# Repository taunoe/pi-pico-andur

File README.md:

# Pi Pico Andur

## Proto 0

- https://www.instagram.com/reel/DPMSu_giLpH/?utm_source=ig_web_copy_link&igsh=MzRlODBiNWFlZA==
- https://www.instagram.com/reel/DPefCeejA3R/?utm_source=ig_web_copy_link&igsh=MzRlODBiNWFlZA==

## Proto 1 Jupid

Pilt|Nimi    | m    | m   |Kood
----|--------|------|-----|----
|RASPBERRY PI PICO 2| Cortex-M33| |SC1631
|ToF / Laser moodul| VL53L0X 3-5VDC| I2C, 0.05÷1.2m | OKYN220420-17
|OLED display| 0.96''| Sinine ja valge| OKY4020
|Toitemoodul DC/DC| step-down |4.75..23V/1..17 3A|OKY3504-1
|Rotary Encoder|-|-| OKY3431
|Makettplaat| 40*60mm |-|OKY0001-1-4X6CM
|Makettplaat| 20*80mm| kahepoolne| OKN426-8
|LED punane matt| 2*5mm| 5mcd| OLC2X5M0005
|LED roheline matt| 2*5mm| 10mcd| LZ2X5M0010
|Takisti | 470R | 1/4W| -
|Optron|EL817C |-| PC817
|Toitepesa paneelile| 2.1/5.5mm| | PC-010
|Pistik| 2.1/5.5mm| 14mm, plast| LUM-XNESJ210
|Signalisatsioonikaabel|8x0.22mm2 |tinatatud Valge|S8X022W
|Lintkaabel| 5*0.3mm2|-| LP05-RGBW
|Piikriba |1*40pin| 2.54mm|CC078
|Piikriba pesa plaadile| 1*20pin |2.54mm |L20420GS
|Kruviklemmliist| 12*2.5mm2| STCM-8471| EL-CONN040B
|2-ne klemmliist pcb| 5.0mm| h=10mm 1.5mm2| TB-001LC
|3-ne klemmiist. pcb| 5.0mm| h=12mm| TB-002
|Ühendusklemm 3-ne| kangiga avatav ja suletav|-| DGBSC-SG01/4-03P
|Ühendusklemm 2-ne| kangiga| läbiv|DGBSC-SG02/4-01P
|Kaablisideme komplekt| 160mm| Värvilised| ECTC160

Tauno Erik 2025

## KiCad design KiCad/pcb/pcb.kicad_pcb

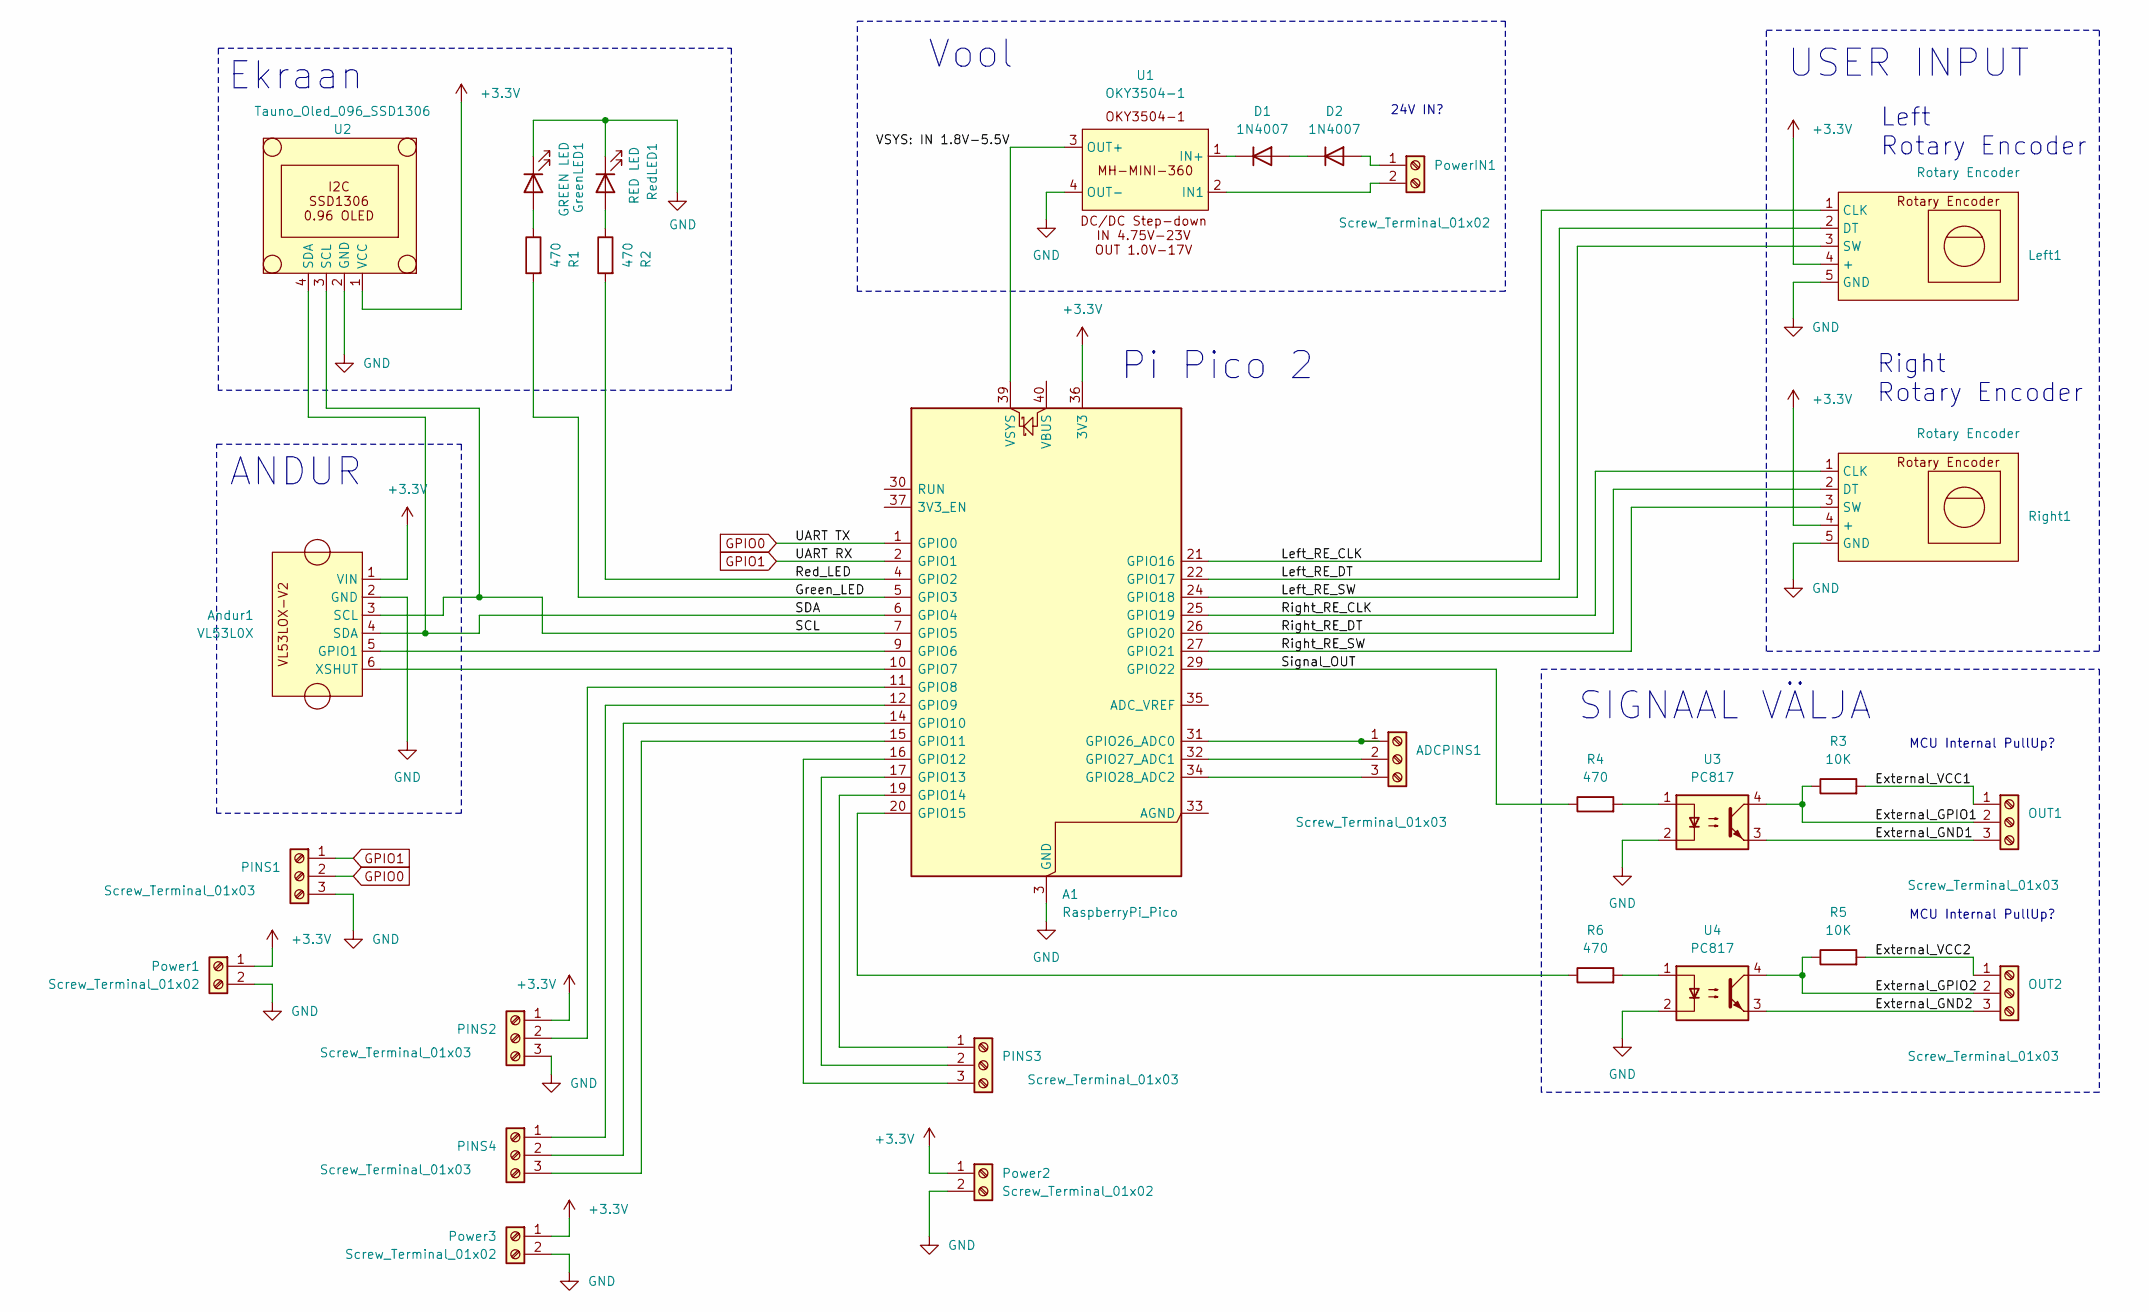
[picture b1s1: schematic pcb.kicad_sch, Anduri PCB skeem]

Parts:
A1: RaspberryPi_Pico; RaspberryPi_Pico_W_SMD_HandSolder
ADCPINS1: Screw_Terminal_01x03; TerminalBlock_MaiXu_MX126-5.0-03P_1x03_P5.00mm
Andur1: VL53L0X; TerminalBlock_MaiXu_MX126-5.0-06P_1x06_P5.00mm
D1, D2: 1N4007; D_DO-41_SOD81_P10.16mm_Horizontal
GreenLED1: GREEN LED; LED_Rectangular_W5.0mm_H2.0mm
Left1: Rotary Encoder; Tauno_Rotary_Encoder
OUT1, OUT2: Screw_Terminal_01x03; TerminalBlock_MaiXu_MX126-5.0-03P_1x03_P5.00mm
PINS1, PINS2, PINS3, PINS4: Screw_Terminal_01x03; TerminalBlock_MaiXu_MX126-5.0-03P_1x03_P5.00mm
Power1, Power2, Power3: Screw_Terminal_01x02; TerminalBlock_MaiXu_MX126-5.0-02P_1x02_P5.00mm
PowerIN1: Screw_Terminal_01x02; TerminalBlock_MaiXu_MX126-5.0-02P_1x02_P5.00mm
R1, R2, R4, R6: 470; R_Axial_DIN0207_L6.3mm_D2.5mm_P10.16mm_Horizontal
R3, R5: 10K; R_Axial_DIN0207_L6.3mm_D2.5mm_P10.16mm_Horizontal
RedLED1: RED LED; LED_Rectangular_W5.0mm_H2.0mm
Right1: Rotary Encoder; Tauno_Rotary_Encoder
U1: OKY3504-1; Tauno_OKY3504
U2: Tauno_Oled_096_SSD1306; Tauno_OLED_ssd1306
U3, U4: PC817; DIP-4_W7.62mm

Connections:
+3.3V: A1.36 (3V3), Andur1.1 (VIN), Left1.4 (+), PINS2.1, Power1.1, Power2.1, Power3.1, Right1.4 (+), U2.1 (VCC)
/External_GND1: OUT1.3, U3.3
/External_GND2: OUT2.3, U4.3
/External_GPIO1: OUT1.2, R3.1, U3.4
/External_GPIO2: OUT2.2, R5.1, U4.4
/External_VCC1: OUT1.1, R3.2
/External_VCC2: OUT2.1, R5.2
/Green_LED: A1.5 (GPIO3), R1.2
/Left_RE_CLK: A1.21 (GPIO16), Left1.1 (CLK)
/Left_RE_DT: A1.22 (GPIO17), Left1.2 (DT)
/Left_RE_SW: A1.24 (GPIO18), Left1.3 (SW)
/Red_LED: A1.4 (GPIO2), R2.2
/Right_RE_CLK: A1.25 (GPIO19), Right1.1 (CLK)
/Right_RE_DT: A1.26 (GPIO20), Right1.2 (DT)
/Right_RE_SW: A1.27 (GPIO21), Right1.3 (SW)
/SCL: A1.7 (GPIO5), Andur1.3 (SCL), U2.3 (SCL)
/SDA: A1.6 (GPIO4), Andur1.4 (SDA), U2.4 (SDA)
/Signal_OUT: A1.29 (GPIO22), R4.1
/VSYS: IN 1.8V-5.5V: A1.39 (VSYS), U1.3 (OUT+)
GND: A1.3 (GND), A1.8 (GND), A1.13 (GND), A1.18 (GND), A1.23 (GND), A1.28 (GND), A1.38 (GND), Andur1.2 (GND), GreenLED1.1 (K), Left1.5 (GND), PINS1.3, PINS2.3, Power1.2, Power2.2, Power3.2, RedLED1.1 (K), Right1.5 (GND), U1.4 (OUT-), U2.2 (GND), U3.2, U4.2
GPIO0: A1.1 (GPIO0), PINS1.2
GPIO1: A1.2 (GPIO1), PINS1.1
unnamed: A1.9 (GPIO6), Andur1.5 (GPIO1)
unnamed: A1.10 (GPIO7), Andur1.6 (XSHUT)
unnamed: A1.11 (GPIO8), PINS2.2
unnamed: A1.12 (GPIO9), PINS4.1
unnamed: A1.14 (GPIO10), PINS4.2
unnamed: A1.15 (GPIO11), PINS4.3
unnamed: A1.16 (GPIO12), PINS3.3
unnamed: A1.17 (GPIO13), PINS3.2
unnamed: A1.19 (GPIO14), PINS3.1
unnamed: A1.20 (GPIO15), R6.1
unnamed: A1.31 (GPIO26_ADC0), ADCPINS1.1
unnamed: A1.32 (GPIO27_ADC1), ADCPINS1.2
unnamed: A1.34 (GPIO28_ADC2), ADCPINS1.3
unnamed: D1.2 (A), D2.1 (K)
unnamed: D1.1 (K), U1.1 (IN+)
unnamed: D2.2 (A), PowerIN1.1
unnamed: GreenLED1.2 (A), R1.1
unnamed: PowerIN1.2, U1.2 (IN1)
unnamed: R4.2, U3.1
unnamed: R6.2, U4.1
unnamed: R2.1, RedLED1.2 (A)

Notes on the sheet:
Right Rotary Encoder
Ekraan
Vool
ANDUR
MCU Internal PullUp?
Pi Pico 2
SIGNAAL VÄLJA
USER INPUT
24V IN?
Left Rotary Encoder

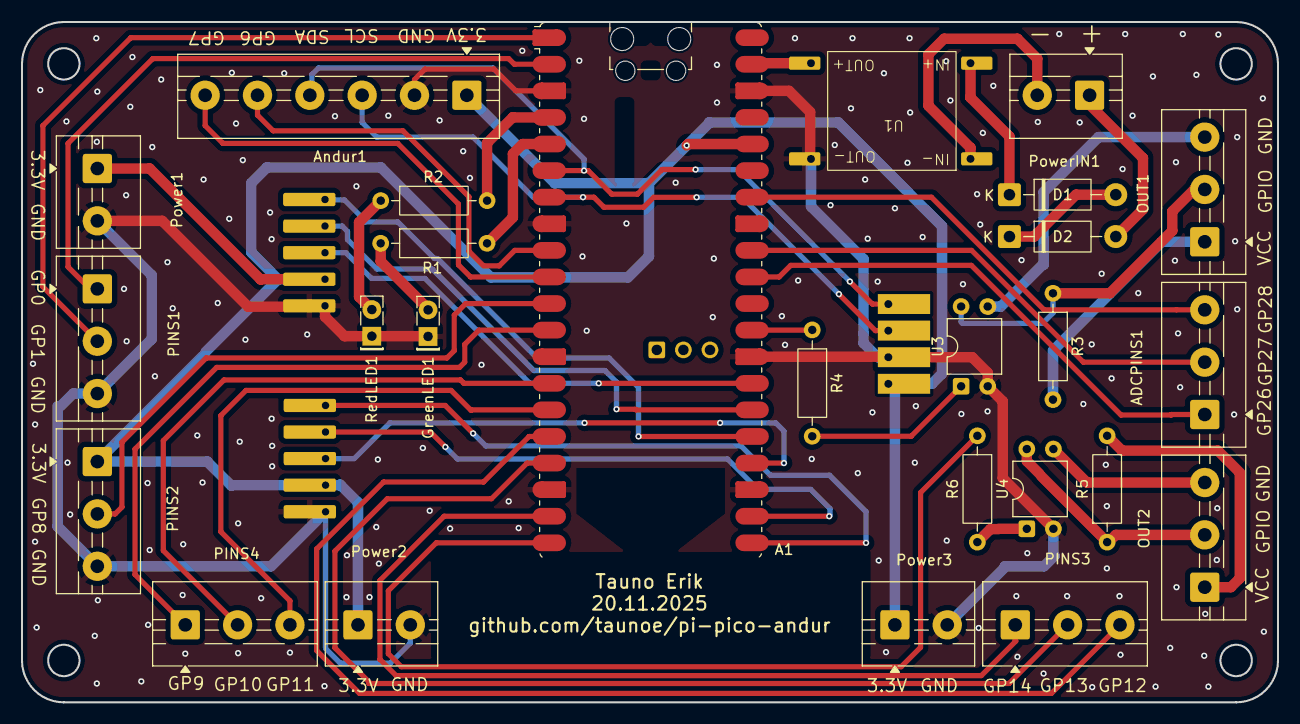
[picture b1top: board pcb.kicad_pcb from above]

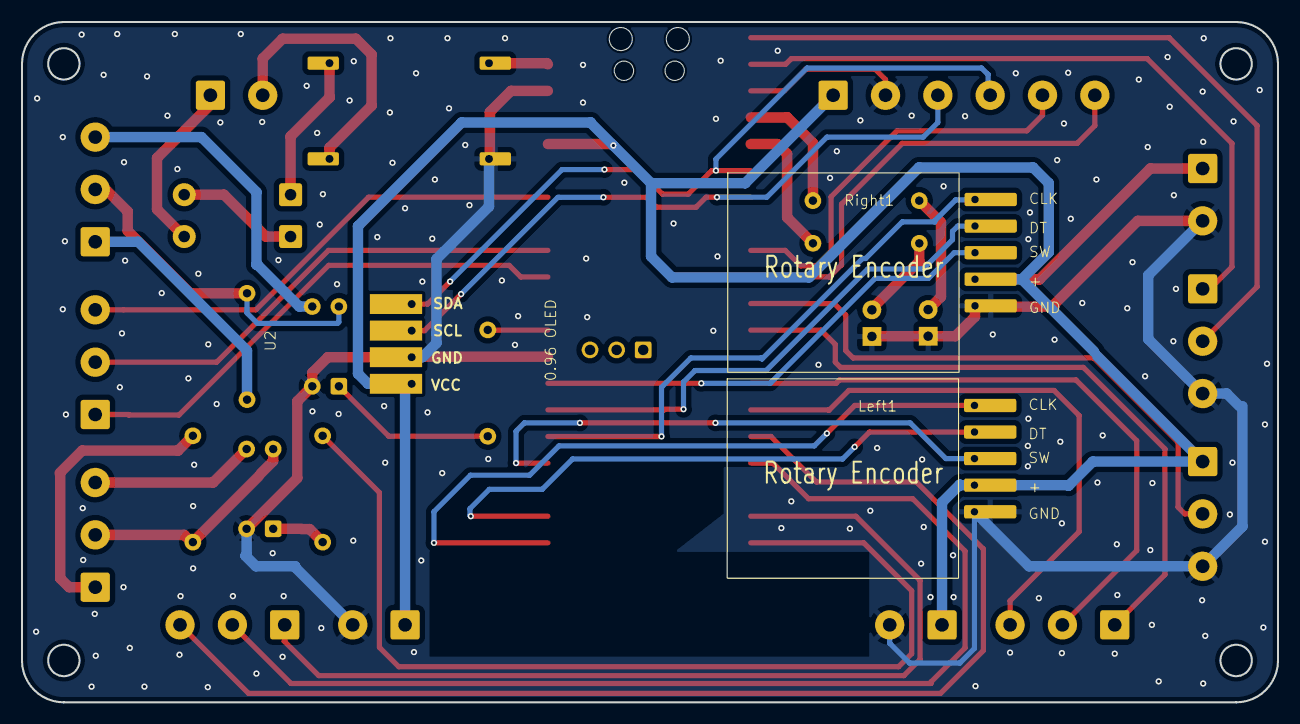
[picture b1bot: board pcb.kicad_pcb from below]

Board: 2 copper layers, 120.0 x 65.0 mm, 29 parts (3 on the bottom side), 43 nets.

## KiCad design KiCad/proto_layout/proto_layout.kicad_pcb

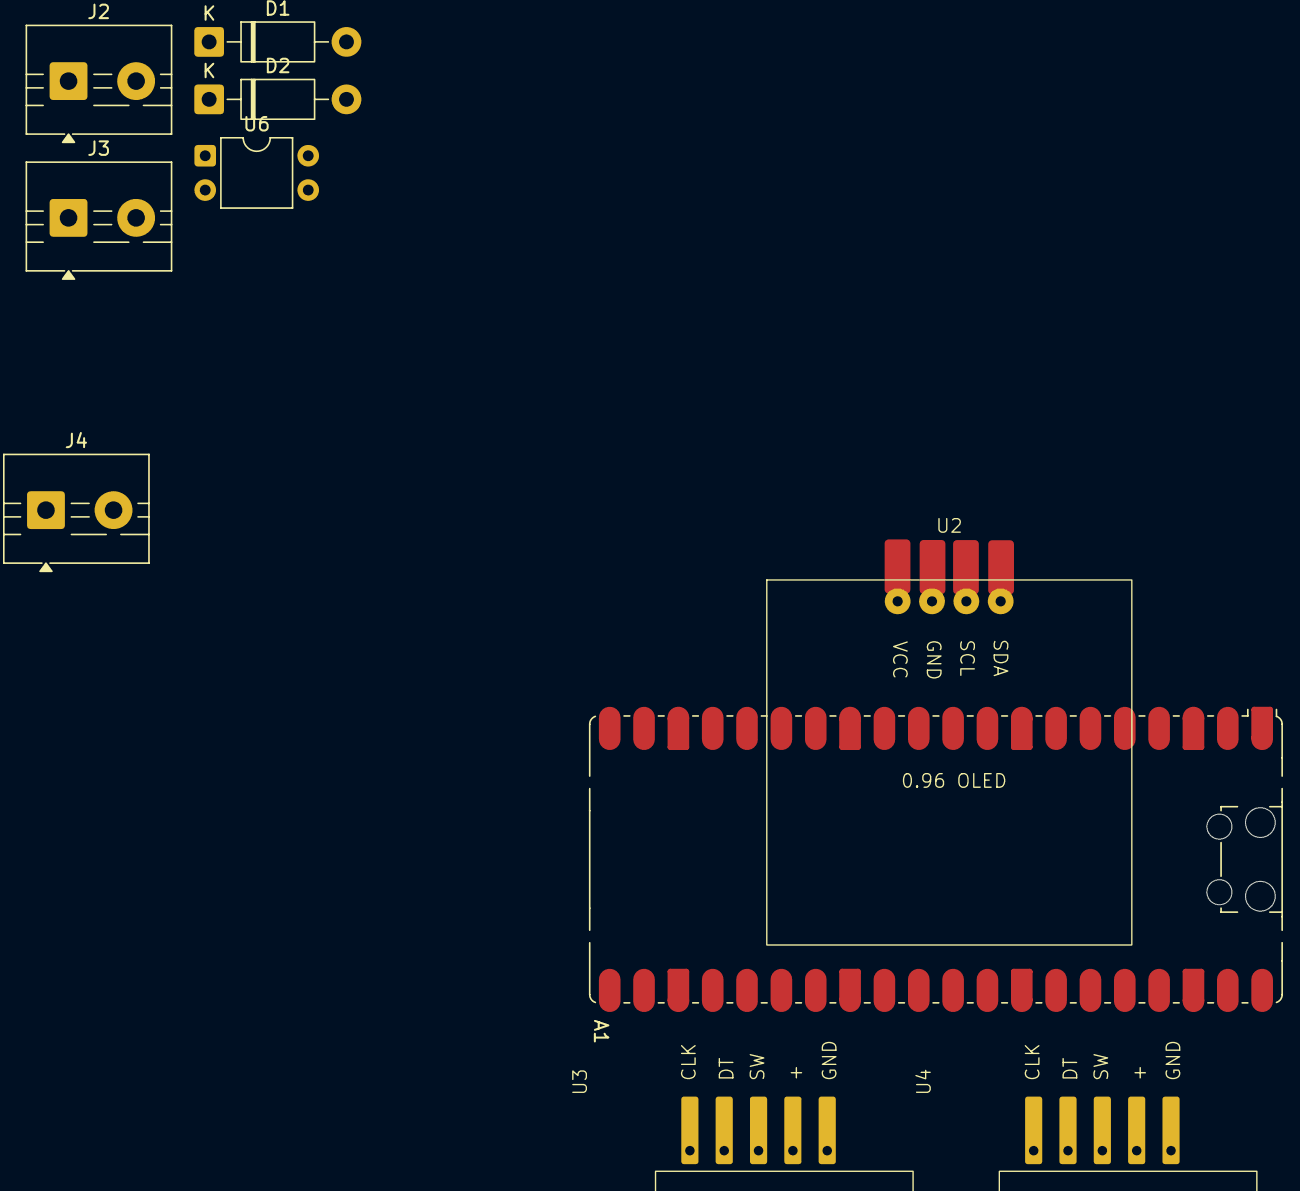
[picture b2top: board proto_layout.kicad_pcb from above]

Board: 2 copper layers, 10 parts (0 on the bottom side), 11 nets, no tracks yet.

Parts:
A1: RaspberryPi_Pico; RaspberryPi_Pico_Common_SMD
D1, D2: 1N4007; D_DO-41_SOD81_P10.16mm_Horizontal
J2, J3, J4: Screw_Terminal_01x02; TerminalBlock_MaiXu_MX126-5.0-02P_1x02_P5.00mm
U2: Tauno_Oled_096_SSD1306; Tauno_OLED_ssd1306
U3, U4: Tauno_Rotary_Encoder
U6: PC817; DIP-4_W7.62mm

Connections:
+3.3V: A1.36 (3V3), U2.1 (VCC), U3.4 (+), U4.4 (+)
GND: A1.3 (GND), A1.8 (GND), A1.13 (GND), A1.18 (GND), A1.23 (GND), A1.28 (GND), A1.38 (GND), U2.2 (GND), U3.5 (GND), U4.5 (GND), U6.2
Left_RE_CLK: A1.21 (GPIO16), U3.1 (CLK)
Left_RE_DT: A1.22 (GPIO17), U3.2 (DT)
Left_RE_SW: A1.24 (GPIO18), U3.3 (SW)
unnamed: D1.2 (A), D2.1 (K)
Right_RE_CLK: A1.25 (GPIO19), U4.1 (CLK)
Right_RE_DT: A1.26 (GPIO20), U4.2 (DT)
Right_RE_SW: A1.27 (GPIO21), U4.3 (SW)
SCL: A1.7 (GPIO5), U2.3 (SCL)
SDA: A1.6 (GPIO4), U2.4 (SDA)

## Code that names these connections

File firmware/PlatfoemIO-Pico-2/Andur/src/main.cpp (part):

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 * - https://learn.adafruit.com/adafruit-vl53l0x-micro-lidar-distance-sensor-breakout/arduino-code
 * - https://github.com/gbr1/rp2040-encoder-library
 *
 * I2C0: SDA GPIOs -> GPIO0, GPIO4, GPIO8, GPIO12, GPIO16, GPIL20
 * I2C0: SCL GPIOs -> GPIO1, GPIO5, GPIO9, GPIO13, GPIO17, GPIO21
 *
 * I2C1: SDA GPIOs -> GPIO2, GPIO6, GPIO10, GPIO14, GPIO18, GPIO26
 * I2C1: SCL GPIOs -> GPIO3, GPIO7, GPIO11, GPIO15, GPIO19, GPIO27
 *
 */

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constexpr int RED = 3;

// I2C
// SDA - GPIO4
// SCL - GPIO5
//constexpr int SENSOR_GPIO1_PIN = 6;  // Used to indicate that data is ready
constexpr int SENSOR_XSHUT_PIN = 7;  // By default it's pulled high. When the pin is pulled low, the sensor goes into shutdown mode.

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
sensor_mode_t sensor_mode = MODE_DEFAULT;

constexpr int GREEN_LED_PIN = GREEN;
constexpr int RED_LED_PIN = RED;

// MIN (Left) Rotary Encoder
constexpr int MIN_RE_CLK_PIN = 19; // 16;
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 Initialises Green and Red LED pins.
 *******************************************************************/
void init_LED_pins() {
  pinMode(GREEN_LED_PIN, OUTPUT);
  pinMode(RED_LED_PIN, OUTPUT);

  digitalWrite(RED_LED_PIN, LOW);
  digitalWrite(GREEN_LED_PIN, LOW);
}


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
  // LED Logic
  if (led_color == RED) {
    digitalWrite(GREEN_LED_PIN, in_range ? HIGH : LOW);
    digitalWrite(RED_LED_PIN, in_range ? LOW : HIGH);
  } else {
    digitalWrite(GREEN_LED_PIN, in_range ? LOW : HIGH);
    digitalWrite(RED_LED_PIN, in_range ? HIGH : LOW);
  }
}

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
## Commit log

2025-11-13 init
2025-11-15 kicad
2025-11-16 kicad update
2025-11-18 ver 1
2025-11-19 3d models
2025-11-23 kicad files
2025-12-02 skeem
2025-12-11 3dmudel
2025-12-11 windows
2025-12-11 [ImgBot] Optimize images
    *Total -- 96.52kb -> 85.59kb (11.32%)
    /img/pocitive_polarity.png -- 12.61kb -> 5.05kb (59.96%)
    /datasheets/Mini360-2d-model.jpg -- 18.31kb -> 17.36kb (5.2%)
    /datasheets/53l0x_SCH.jpg -- 65.59kb -> 63.18kb (3.68%)
2025-12-12 uus library
2025-12-14 small
2025-12-19 enkooder
2026-01-02 min,max and btns
2026-01-06 mingi error
2026-01-07 it works
2026-01-07 puhastatud
2026-01-07 high accuracy mode
2026-01-08 Karp v2
2026-01-14 box ver 2
2026-01-20 4mm ja anduri mudel
2026-01-20 uued dxfid
2026-03-13 error blink
